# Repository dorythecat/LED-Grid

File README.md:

# LED-Grid
A simple battery-powered LED grid a friend asked me to design for them, so they could put a vinyl decoration on top for conventions and stuff. The BOM included is for JLC, since it's what this prototype is designed for. Just plug a battery in and on your merry way :D

It's meant to be housed on a (yet to design) 3D printed case that will have a slot on the front for interchangeable vinyls to display as a con badge. It's powerful enough to blind you at short distance, and should be pretty good at dissipating heat. just make sure your battery is above 2500mAh and you'll be good for around 8 hours or so! :D

# 3D Render

# BOM

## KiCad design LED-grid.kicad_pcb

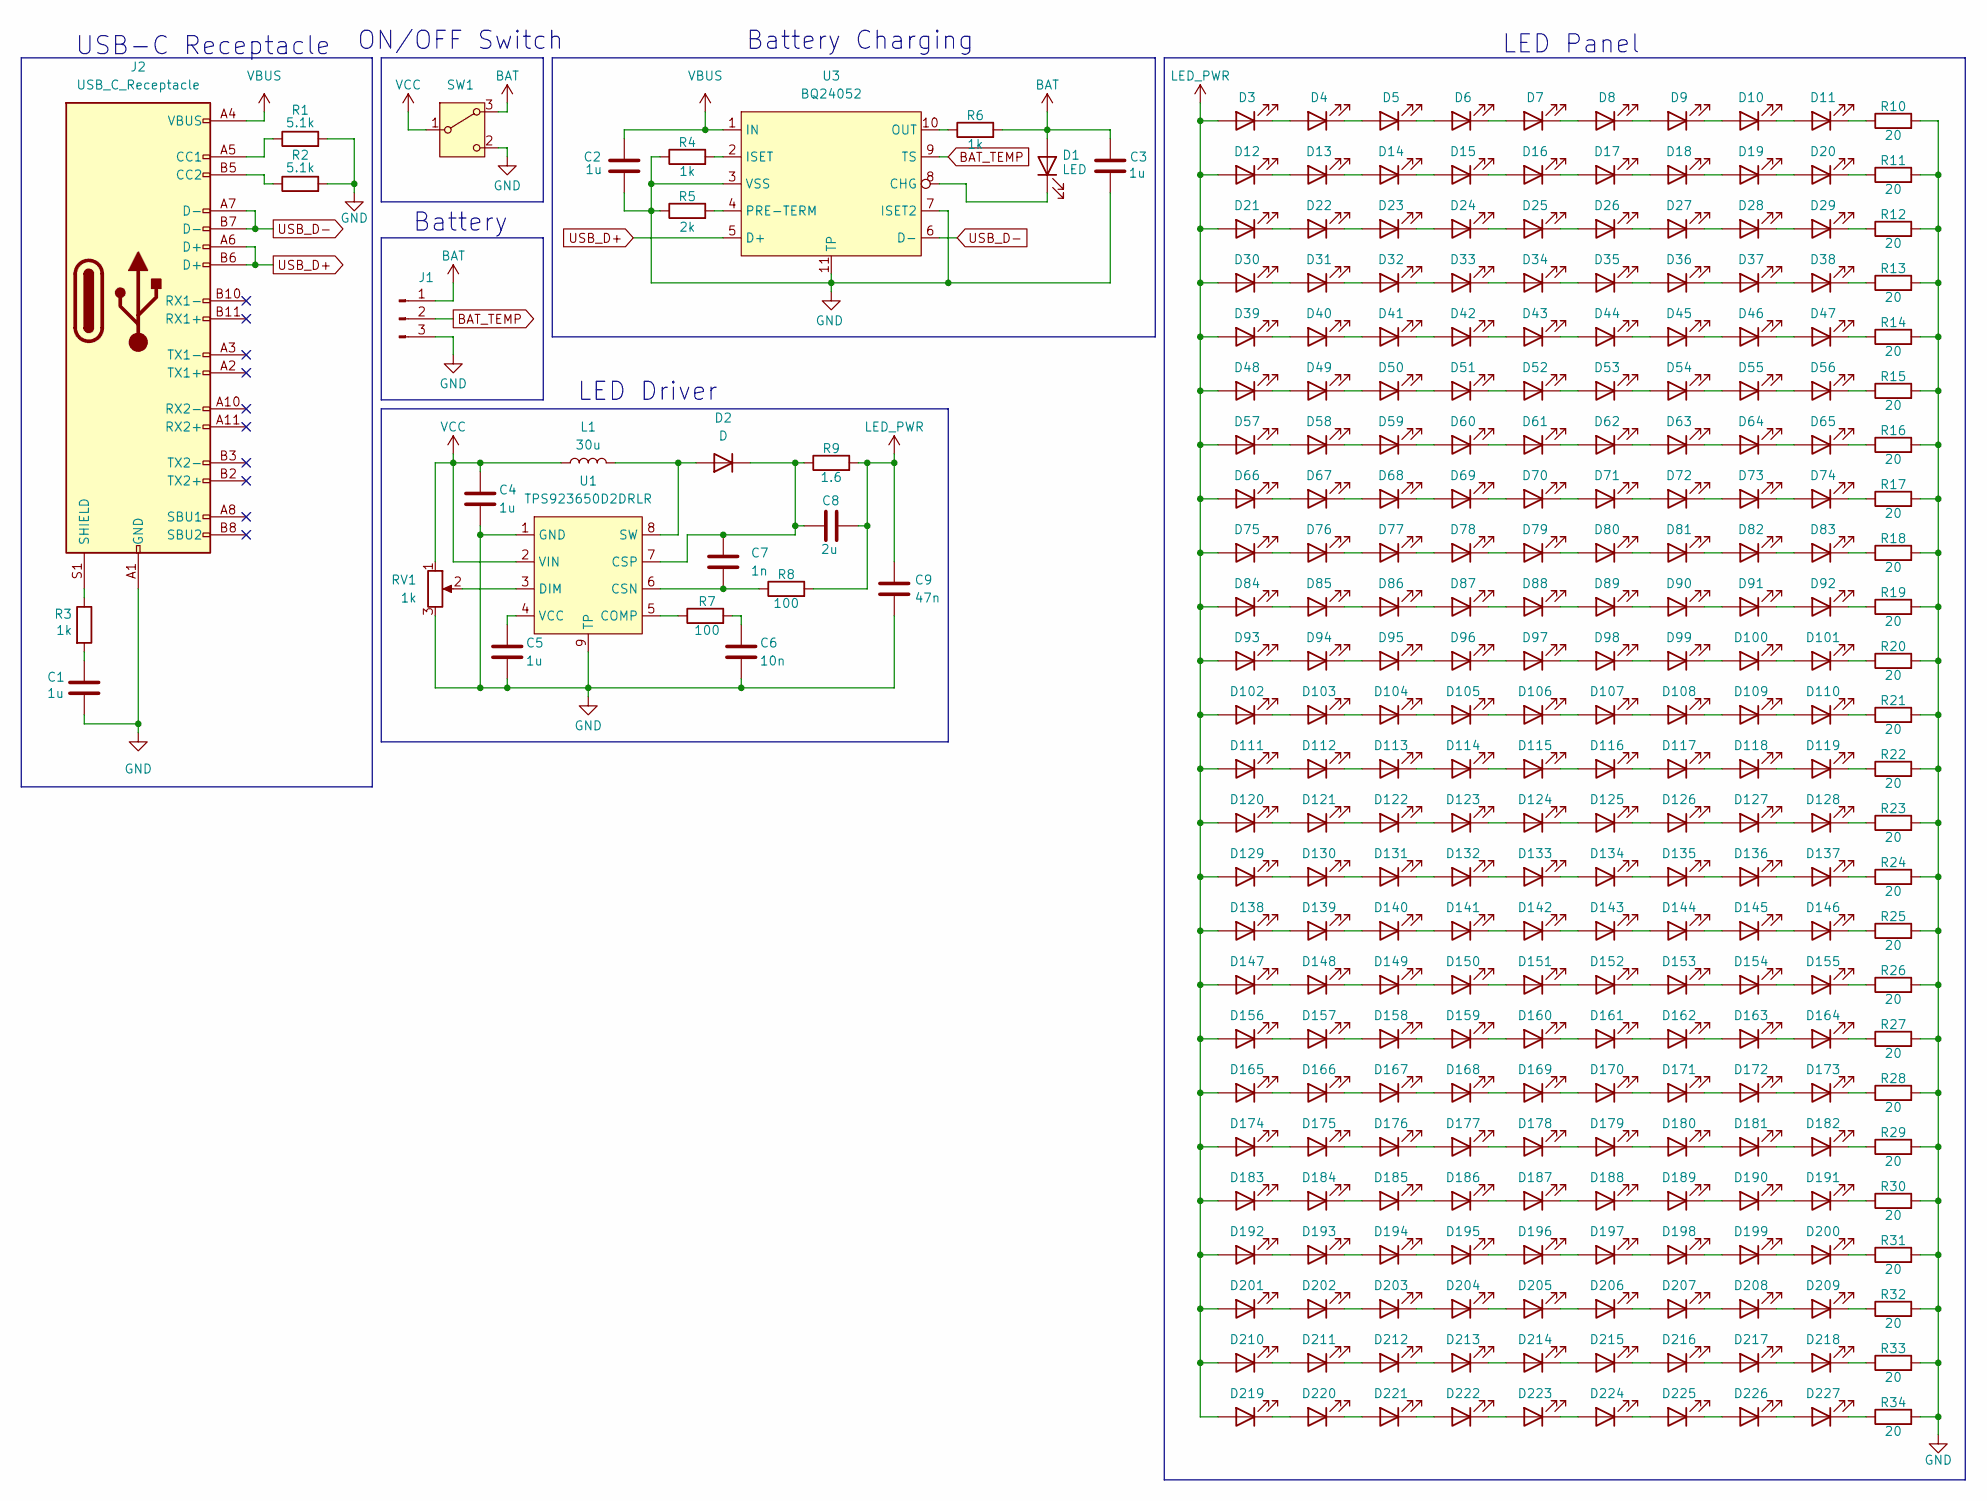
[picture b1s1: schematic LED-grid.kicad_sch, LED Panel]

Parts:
C1, C2, C3, C4, C5: 1u; C_0603_1608Metric
C6: 10n; C_0603_1608Metric
C7: 1n; C_0201_0603Metric
C8: 2u; C_0603_1608Metric
C9: 47n; C_0201_0603Metric
D1, D3, D4, D5, D6, D7, D8, D9, D10, D11, D12, D13, D14, D15, D16, D17, D18, D19, D20, D21, D22, D23, D24, D25, D26, D27, D28, D29, D30, D31, D32, D33, D34, D35, D36, D37, D38, D39, D40, D41, D42, D43, D44, D45, D46, D47, D48, D49, D50, D51, D52, D53, D54, D55, D56, D57, D58, D59, D60, D61, D62, D63, D64, D65, D66, D67, D68, D69, D70, D71, D72, D73, D74, D75, D76, D77, D78, D79, D80, D81, D82, D83, D84, D85, D86, D87, D88, D89, D90, D91, D92, D93, D94, D95, D96, D97, D98, D99, D100, D101, D102, D103, D104, D105, D106, D107, D108, D109, D110, D111, D112, D113, D114, D115, D116, D117, D118, D119, D120, D121, D122, D123, D124, D125, D126, D127, D128, D129, D130, D131, D132, D133, D134, D135, D136, D137, D138, D139, D140, D141, D142, D143, D144, D145, D146, D147, D148, D149, D150, D151, D152, D153, D154, D155, D156, D157, D158, D159, D160, D161, D162, D163, D164, D165, D166, D167, D168, D169, D170, D171, D172, D173, D174, D175, D176, D177, D178, D179, D180, D181, D182, D183, D184, D185, D186, D187, D188, D189, D190, D191, D192, D193, D194, D195, D196, D197, D198, D199, D200, D201, D202, D203, D204, D205, D206, D207, D208, D209, D210, D211, D212, D213, D214, D215, D216, D217, D218, D219, D220, D221, D222, D223, D224, D225, D226, D227: LED; LED_0603_1608Metric
D2: D; D_0603_1608Metric
J1: Conn_01x03_Pin; JST_ZH_B3B-ZR_1x03_P1.50mm_Vertical
J2: USB_C_Receptacle; USB_C_Receptacle_Amphenol_12401610E4-2A
L1: 30u
R1, R2: 5.1k; R_0201_0603Metric
R3, R4, R6: 1k; R_0201_0603Metric
R5: 2k; R_0201_0603Metric
R7, R8: 100; R_0201_0603Metric
R9: 1.6; R_0201_0603Metric
R10, R11, R12, R13, R14, R15, R16, R17, R18, R19, R20, R21, R22, R23, R24, R25, R26, R27, R28, R29, R30, R31, R32, R33, R34: 20; R_0201_0603Metric
RV1: 1k; Potentiometer_Bourns_3386P_Vertical
SW1: SW_Wuerth_450301014042; SW_Slide-03_Wuerth-WS-SLTV_10x2.5x6.4_P2.54mm
U1: TPS923650D2DRLR; WSON-8-1EP_2x2mm_P0.5mm_EP0.9x1.6mm_ThermalVias
U3: BQ24052; WSON-10-1EP_2.5x2.5mm_P0.5mm_EP1.2x2mm_ThermalVias

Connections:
BAT: C3.2, D1.2 (A), J1.1, R6.2, SW1.3 (A)
BAT_TEMP: J1.2, U3.9 (TS)
GND: C1.2, C2.2, C3.1, C4.2, C5.2, C6.2, C9.2, J1.3, J2.A1 (GND), J2.A12 (GND), J2.B1 (GND), J2.B12 (GND), R1.2, R2.2, R4.1, R5.1, R10.2, R11.2, R12.2, R13.2, R14.2, R15.2, R16.2, R17.2, R18.2, R19.2, R20.2, R21.2, R22.2, R23.2, R24.2, R25.2, R26.2, R27.2, R28.2, R29.2, R30.2, R31.2, R32.2, R33.2, R34.2, RV1.3, SW1.2 (C), U1.1 (GND), U1.9 (TP), U3.3 (VSS), U3.7 (ISET2), U3.11 (TP)
LED_PWR: C8.2, C9.1, D3.2 (A), D12.2 (A), D21.2 (A), D30.2 (A), D39.2 (A), D48.2 (A), D57.2 (A), D66.2 (A), D75.2 (A), D84.2 (A), D93.2 (A), D102.2 (A), D111.2 (A), D120.2 (A), D129.2 (A), D138.2 (A), D147.2 (A), D156.2 (A), D165.2 (A), D174.2 (A), D183.2 (A), D192.2 (A), D201.2 (A), D210.2 (A), D219.2 (A), R8.2, R9.2
unnamed: C1.1, R3.2
unnamed: C6.1, R7.2
unnamed: D1.1 (K), U3.8 (CHG)
unnamed: D2.2 (A), L1.2, U1.8 (SW)
unnamed: C7.1, C8.1, D2.1 (K), R9.1, U1.7 (CSP)
unnamed: D3.1 (K), D4.2 (A)
unnamed: D4.1 (K), D5.2 (A)
unnamed: D5.1 (K), D6.2 (A)
unnamed: D6.1 (K), D7.2 (A)
unnamed: D7.1 (K), D8.2 (A)
unnamed: D8.1 (K), D9.2 (A)
unnamed: D9.1 (K), D10.2 (A)
unnamed: D10.1 (K), D11.2 (A)
unnamed: D11.1 (K), R10.1
unnamed: D12.1 (K), D13.2 (A)
unnamed: D13.1 (K), D14.2 (A)
unnamed: D14.1 (K), D15.2 (A)
unnamed: D15.1 (K), D16.2 (A)
unnamed: D16.1 (K), D17.2 (A)
unnamed: D17.1 (K), D18.2 (A)
unnamed: D18.1 (K), D19.2 (A)
unnamed: D19.1 (K), D20.2 (A)
unnamed: D20.1 (K), R11.1
unnamed: D21.1 (K), D22.2 (A)
unnamed: D22.1 (K), D23.2 (A)
unnamed: D23.1 (K), D24.2 (A)
unnamed: D24.1 (K), D25.2 (A)
unnamed: D25.1 (K), D26.2 (A)
unnamed: D26.1 (K), D27.2 (A)
unnamed: D27.1 (K), D28.2 (A)
unnamed: D28.1 (K), D29.2 (A)
unnamed: D29.1 (K), R12.1
unnamed: D30.1 (K), D31.2 (A)
unnamed: D31.1 (K), D32.2 (A)
unnamed: D32.1 (K), D33.2 (A)
unnamed: D33.1 (K), D34.2 (A)
unnamed: D34.1 (K), D35.2 (A)
unnamed: D35.1 (K), D36.2 (A)
unnamed: D36.1 (K), D37.2 (A)
unnamed: D37.1 (K), D38.2 (A)
unnamed: D38.1 (K), R13.1
unnamed: D39.1 (K), D40.2 (A)
unnamed: D40.1 (K), D41.2 (A)
unnamed: D41.1 (K), D42.2 (A)
unnamed: D42.1 (K), D43.2 (A)
unnamed: D43.1 (K), D44.2 (A)
unnamed: D44.1 (K), D45.2 (A)
unnamed: D45.1 (K), D46.2 (A)
unnamed: D46.1 (K), D47.2 (A)
unnamed: D47.1 (K), R14.1
unnamed: D48.1 (K), D49.2 (A)
unnamed: D49.1 (K), D50.2 (A)
unnamed: D50.1 (K), D51.2 (A)
unnamed: D51.1 (K), D52.2 (A)
unnamed: D52.1 (K), D53.2 (A)
unnamed: D53.1 (K), D54.2 (A)
unnamed: D54.1 (K), D55.2 (A)
unnamed: D55.1 (K), D56.2 (A)
unnamed: D56.1 (K), R15.1
unnamed: D57.1 (K), D58.2 (A)
unnamed: D58.1 (K), D59.2 (A)
unnamed: D59.1 (K), D60.2 (A)
unnamed: D60.1 (K), D61.2 (A)
unnamed: D61.1 (K), D62.2 (A)
unnamed: D62.1 (K), D63.2 (A)
unnamed: D63.1 (K), D64.2 (A)
unnamed: D64.1 (K), D65.2 (A)
unnamed: D65.1 (K), R16.1
unnamed: D66.1 (K), D67.2 (A)
unnamed: D67.1 (K), D68.2 (A)
unnamed: D68.1 (K), D69.2 (A)
unnamed: D69.1 (K), D70.2 (A)
unnamed: D70.1 (K), D71.2 (A)
unnamed: D71.1 (K), D72.2 (A)
unnamed: D72.1 (K), D73.2 (A)
unnamed: D73.1 (K), D74.2 (A)
unnamed: D74.1 (K), R17.1
unnamed: D75.1 (K), D76.2 (A)
unnamed: D76.1 (K), D77.2 (A)
unnamed: D77.1 (K), D78.2 (A)
unnamed: D78.1 (K), D79.2 (A)
unnamed: D79.1 (K), D80.2 (A)
unnamed: D80.1 (K), D81.2 (A)
unnamed: D81.1 (K), D82.2 (A)
unnamed: D82.1 (K), D83.2 (A)
unnamed: D83.1 (K), R18.1
unnamed: D84.1 (K), D85.2 (A)
unnamed: D85.1 (K), D86.2 (A)
unnamed: D86.1 (K), D87.2 (A)
unnamed: D87.1 (K), D88.2 (A)
unnamed: D88.1 (K), D89.2 (A)
unnamed: D89.1 (K), D90.2 (A)
unnamed: D90.1 (K), D91.2 (A)
unnamed: D91.1 (K), D92.2 (A)
unnamed: D92.1 (K), R19.1
unnamed: D93.1 (K), D94.2 (A)
unnamed: D94.1 (K), D95.2 (A)
unnamed: D95.1 (K), D96.2 (A)
unnamed: D96.1 (K), D97.2 (A)
unnamed: D97.1 (K), D98.2 (A)
unnamed: D98.1 (K), D99.2 (A)
unnamed: D99.1 (K), D100.2 (A)
unnamed: D100.1 (K), D101.2 (A)
unnamed: D101.1 (K), R20.1
unnamed: D102.1 (K), D103.2 (A)
unnamed: D103.1 (K), D104.2 (A)
unnamed: D104.1 (K), D105.2 (A)
unnamed: D105.1 (K), D106.2 (A)
unnamed: D106.1 (K), D107.2 (A)
unnamed: D107.1 (K), D108.2 (A)
unnamed: D108.1 (K), D109.2 (A)
unnamed: D109.1 (K), D110.2 (A)
unnamed: D110.1 (K), R21.1
unnamed: D111.1 (K), D112.2 (A)
unnamed: D112.1 (K), D113.2 (A)
unnamed: D113.1 (K), D114.2 (A)
unnamed: D114.1 (K), D115.2 (A)
unnamed: D115.1 (K), D116.2 (A)
unnamed: D116.1 (K), D117.2 (A)
unnamed: D117.1 (K), D118.2 (A)
unnamed: D118.1 (K), D119.2 (A)
unnamed: D119.1 (K), R22.1
unnamed: D120.1 (K), D121.2 (A)
unnamed: D121.1 (K), D122.2 (A)
unnamed: D122.1 (K), D123.2 (A)
unnamed: D123.1 (K), D124.2 (A)
unnamed: D124.1 (K), D125.2 (A)
unnamed: D125.1 (K), D126.2 (A)
unnamed: D126.1 (K), D127.2 (A)
unnamed: D127.1 (K), D128.2 (A)
unnamed: D128.1 (K), R23.1
unnamed: D129.1 (K), D130.2 (A)
unnamed: D130.1 (K), D131.2 (A)
unnamed: D131.1 (K), D132.2 (A)
unnamed: D132.1 (K), D133.2 (A)
unnamed: D133.1 (K), D134.2 (A)
unnamed: D134.1 (K), D135.2 (A)
unnamed: D135.1 (K), D136.2 (A)
unnamed: D136.1 (K), D137.2 (A)
unnamed: D137.1 (K), R24.1
unnamed: D138.1 (K), D139.2 (A)
unnamed: D139.1 (K), D140.2 (A)
unnamed: D140.1 (K), D141.2 (A)
unnamed: D141.1 (K), D142.2 (A)
unnamed: D142.1 (K), D143.2 (A)
unnamed: D143.1 (K), D144.2 (A)
unnamed: D144.1 (K), D145.2 (A)
unnamed: D145.1 (K), D146.2 (A)
unnamed: D146.1 (K), R25.1
unnamed: D147.1 (K), D148.2 (A)
unnamed: D148.1 (K), D149.2 (A)
unnamed: D149.1 (K), D150.2 (A)
unnamed: D150.1 (K), D151.2 (A)
unnamed: D151.1 (K), D152.2 (A)
unnamed: D152.1 (K), D153.2 (A)
unnamed: D153.1 (K), D154.2 (A)
unnamed: D154.1 (K), D155.2 (A)
unnamed: D155.1 (K), R26.1
unnamed: D156.1 (K), D157.2 (A)
unnamed: D157.1 (K), D158.2 (A)
unnamed: D158.1 (K), D159.2 (A)
unnamed: D159.1 (K), D160.2 (A)
unnamed: D160.1 (K), D161.2 (A)
unnamed: D161.1 (K), D162.2 (A)
unnamed: D162.1 (K), D163.2 (A)
unnamed: D163.1 (K), D164.2 (A)
unnamed: D164.1 (K), R27.1
unnamed: D165.1 (K), D166.2 (A)
unnamed: D166.1 (K), D167.2 (A)
unnamed: D167.1 (K), D168.2 (A)
unnamed: D168.1 (K), D169.2 (A)
unnamed: D169.1 (K), D170.2 (A)
unnamed: D170.1 (K), D171.2 (A)
unnamed: D171.1 (K), D172.2 (A)
unnamed: D172.1 (K), D173.2 (A)
unnamed: D173.1 (K), R28.1
unnamed: D174.1 (K), D175.2 (A)
unnamed: D175.1 (K), D176.2 (A)
unnamed: D176.1 (K), D177.2 (A)
unnamed: D177.1 (K), D178.2 (A)
unnamed: D178.1 (K), D179.2 (A)
unnamed: D179.1 (K), D180.2 (A)
unnamed: D180.1 (K), D181.2 (A)
unnamed: D181.1 (K), D182.2 (A)
unnamed: D182.1 (K), R29.1
unnamed: D183.1 (K), D184.2 (A)
unnamed: D184.1 (K), D185.2 (A)
unnamed: D185.1 (K), D186.2 (A)
unnamed: D186.1 (K), D187.2 (A)
unnamed: D187.1 (K), D188.2 (A)
unnamed: D188.1 (K), D189.2 (A)
unnamed: D189.1 (K), D190.2 (A)
unnamed: D190.1 (K), D191.2 (A)
unnamed: D191.1 (K), R30.1
unnamed: D192.1 (K), D193.2 (A)
unnamed: D193.1 (K), D194.2 (A)
unnamed: D194.1 (K), D195.2 (A)
unnamed: D195.1 (K), D196.2 (A)
unnamed: D196.1 (K), D197.2 (A)
unnamed: D197.1 (K), D198.2 (A)
unnamed: D198.1 (K), D199.2 (A)
unnamed: D199.1 (K), D200.2 (A)
unnamed: D200.1 (K), R31.1
unnamed: D201.1 (K), D202.2 (A)
unnamed: D202.1 (K), D203.2 (A)
unnamed: D203.1 (K), D204.2 (A)
unnamed: D204.1 (K), D205.2 (A)
unnamed: D205.1 (K), D206.2 (A)
unnamed: D206.1 (K), D207.2 (A)
unnamed: D207.1 (K), D208.2 (A)
unnamed: D208.1 (K), D209.2 (A)
unnamed: D209.1 (K), R32.1
unnamed: D210.1 (K), D211.2 (A)
unnamed: D211.1 (K), D212.2 (A)
unnamed: D212.1 (K), D213.2 (A)
unnamed: D213.1 (K), D214.2 (A)
unnamed: D214.1 (K), D215.2 (A)
unnamed: D215.1 (K), D216.2 (A)
unnamed: D216.1 (K), D217.2 (A)
unnamed: D217.1 (K), D218.2 (A)
unnamed: D218.1 (K), R33.1
unnamed: D219.1 (K), D220.2 (A)
unnamed: D220.1 (K), D221.2 (A)
unnamed: D221.1 (K), D222.2 (A)
unnamed: D222.1 (K), D223.2 (A)
unnamed: D223.1 (K), D224.2 (A)
unnamed: D224.1 (K), D225.2 (A)
unnamed: D225.1 (K), D226.2 (A)
unnamed: D226.1 (K), D227.2 (A)
unnamed: D227.1 (K), R34.1
unnamed: J2.A5 (CC1), R1.1
unnamed: J2.B5 (CC2), R2.1
unnamed: J2.S1 (SHIELD), R3.1
unnamed: R7.1, U1.5 (COMP)
unnamed: C7.2, R8.1, U1.6 (CSN)
unnamed: RV1.2, U1.3 (DIM)
unnamed: C5.1, U1.4 (VCC)
unnamed: R4.2, U3.2 (ISET)
unnamed: R6.1, U3.10 (OUT)
unnamed: R5.2, U3.4 (PRE-TERM)
USB_D+: J2.A6 (D+), J2.B6 (D+), U3.5 (D+)
USB_D-: J2.A7 (D-), J2.B7 (D-), U3.6 (D-)
VBUS: C2.1, J2.A4 (VBUS), J2.A9 (VBUS), J2.B4 (VBUS), J2.B9 (VBUS), U3.1 (IN)
VCC: C4.1, L1.1, RV1.1, SW1.1 (B), U1.2 (VIN)

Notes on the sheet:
Battery Charging
ON/OFF Switch
LED Panel
LED Driver
USB-C Receptacle
Battery

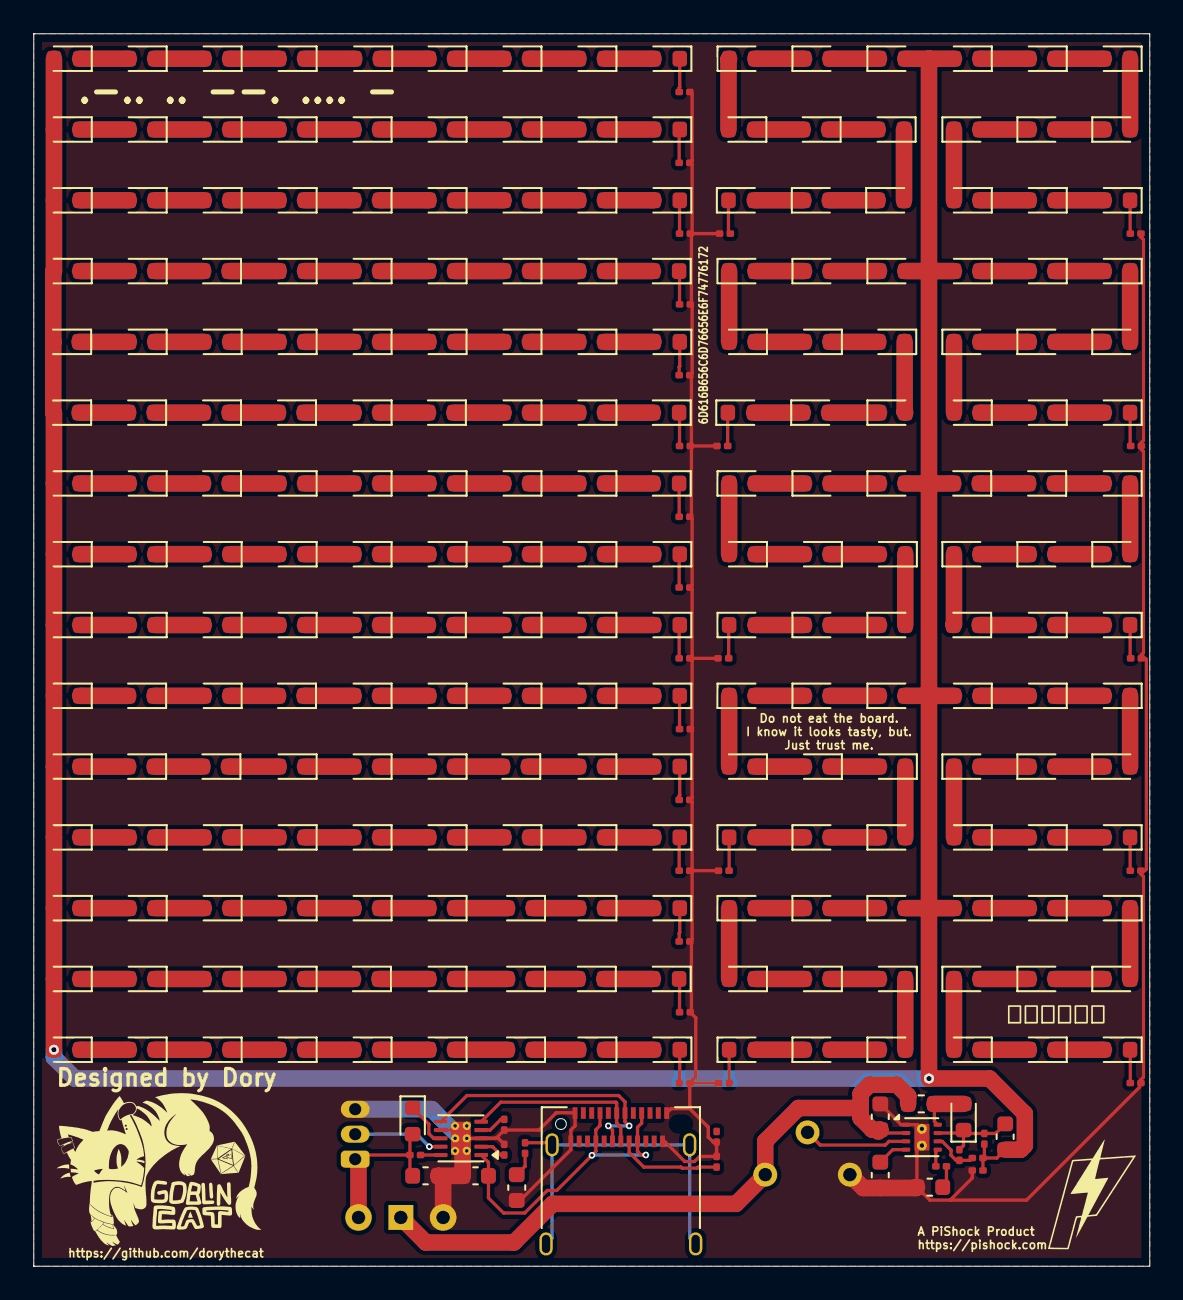
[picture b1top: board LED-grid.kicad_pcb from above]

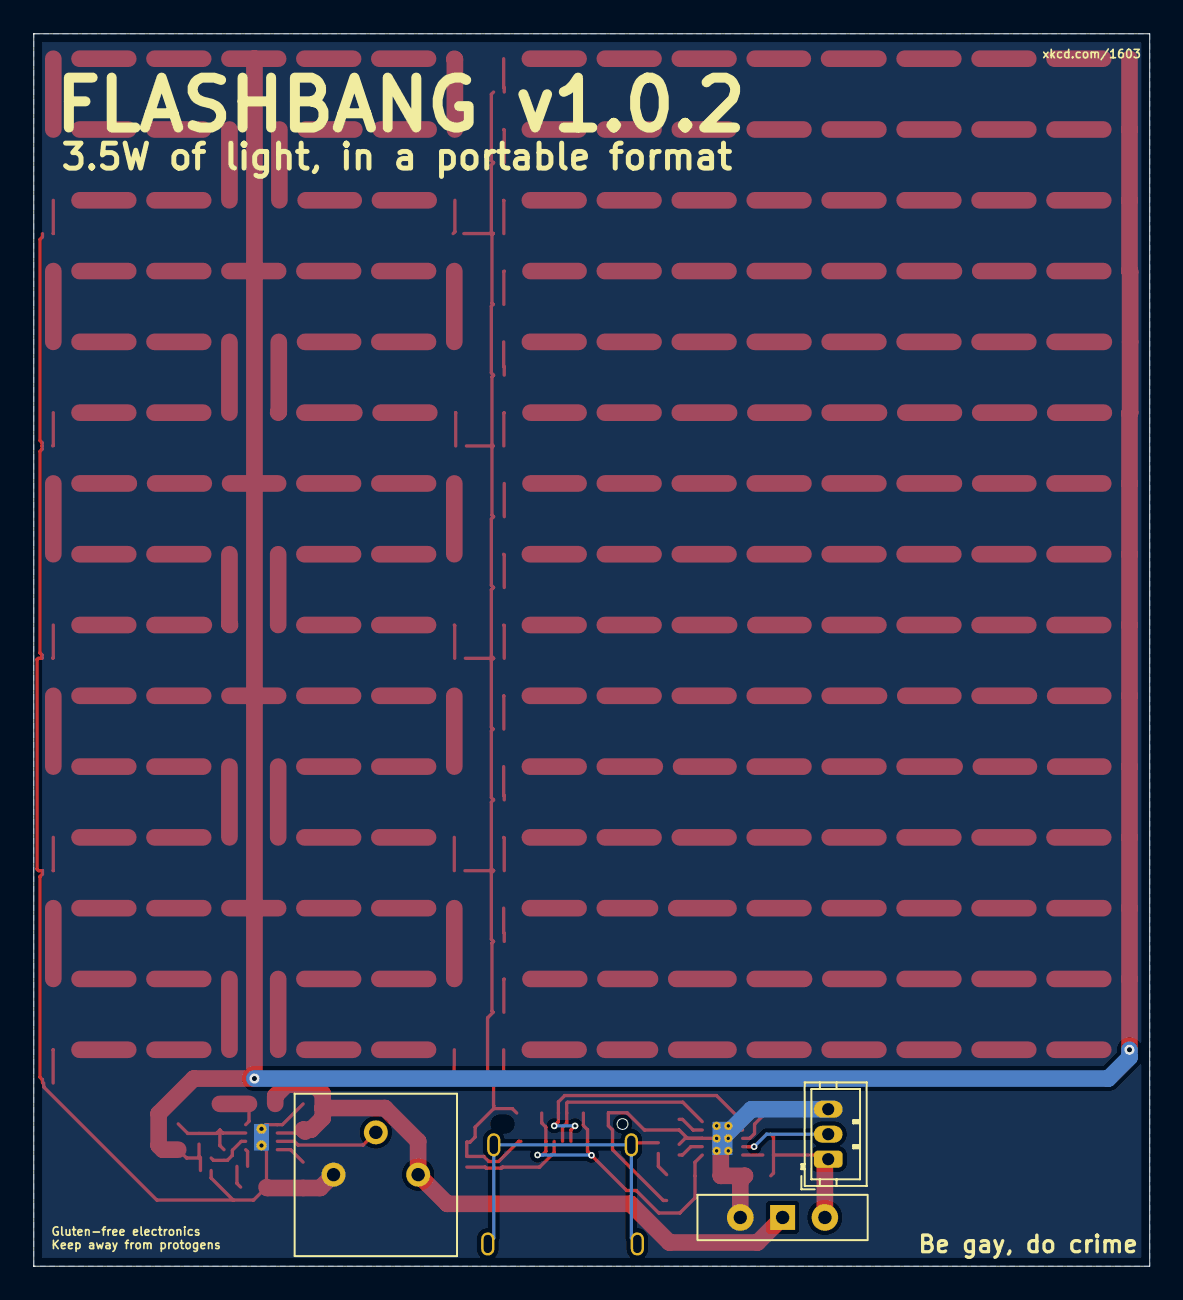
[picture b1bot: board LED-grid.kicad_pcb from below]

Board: 2 copper layers, 67.0 x 74.0 mm, 277 parts (3 on the bottom side), 248 nets.

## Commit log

2026-01-25 Added .gitignore
2026-01-25 Added basic KiCad files
2026-01-25 Finished schematic
2026-01-25 Updated battery footprint
2026-01-25 Finished laying out PCB
2026-01-26 Version 1.0.1 We can now actually control the brightness using a potentiometer
2026-01-27 Updated schematic
2026-01-27 Updated PCB
2026-01-28 Final touches to PCB
2026-02-17 Added .step file
